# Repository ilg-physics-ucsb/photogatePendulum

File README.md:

# Photogate Pendulum

This repository should hold everything related to the photgates made by the ILG for recording more precise data on a pendulum setup. These photogates were made using off the shelf components from adafruit and amazon and mcmaster using a 3D printed case and a CNC milled PCB. For information on components visit the documentation folder, for information on the case or the ciruit visit the hardware folder and for information on the code visit the code folder. 

## Assembly Instructions

**Materials required** 

* **Integrated Circuits**
* 1x [Adafruit ItsyBitsy M0](https://www.digikey.com/en/products/detail/adafruit-industries-llc/3727/8346575?s=N4IgTCBcDaIIYBM4DMBOBXAlgFwAQ4GcBPXAI0JIFkAGEAXQF8g)
* 1x [LM358 Op Amp DIP-8](https://www.digikey.com/en/products/detail/texas-instruments/LM358P/277042)
* **Transistors**
* 6x [2N3904 NPN BJT](https://www.digikey.com/en/products/detail/diotec-semiconductor/2N3904/13164701)
* 1x [Phototransistor 3mm](https://www.digikey.com/en/products/detail/vishay-semiconductor-opto-division/BPW85A/4071264?s=N4IgTCBcDaIEIAUDqAOArAQRAXQL5A)
* **Diodes**
* 1x [IR LED 5mm](https://www.digikey.com/en/products/detail/vishay-semiconductor-opto-division/TSHF6210/4073549)
* 1x [Blue LED 5mm](https://www.digikey.com/en/products/detail/w%C3%BCrth-elektronik/151051BS04000/4490009)
* 1x [1N4148 Diode](https://www.digikey.com/en/products/detail/onsemi/1N4148/458603)
* **Capacitors**
* 5x [1nF](https://www.digikey.com/en/products/detail/kemet/R82EC1100SH50J/5141859)
* 1x [10nF](https://www.digikey.com/en/products/detail/kemet/R82EC2100AA50J/2571307)
* **Resistors**
* 3x [220Ω](https://www.digikey.com/en/products/detail/stackpole-electronics-inc/CF14JT220R/1741346) 
* 1x [1kΩ](https://www.digikey.com/en/products/detail/stackpole-electronics-inc/CF14JT1K00/1741314) 
* 2x [2.2kΩ](https://www.digikey.com/en/products/detail/stackpole-electronics-inc/CF14JT2K20/1741321)
* 9x [10kΩ](https://www.digikey.com/en/products/detail/stackpole-electronics-inc/CF14JT10K0/1741265)
* 2x [22kΩ](https://www.digikey.com/en/products/detail/stackpole-electronics-inc/CF14JT22K0/1741350)
* 3x [100kΩ](https://www.digikey.com/en/products/detail/stackpole-electronics-inc/CF14JT100K/1741263)
* 1x [220kΩ](https://www.digikey.com/en/products/detail/stackpole-electronics-inc/CF14JT220K/1741348)
* 2x [1MΩ](https://www.digikey.com/en/products/detail/stackpole-electronics-inc/CF14JT1M00/1741316) 
* **Tactile**
* 1x [Slide Switch SPDT H6mm](https://www.digikey.com/en/products/detail/same-sky-formerly-cui-devices/SLW-1298856-5A-RA-N-D/24399327)
* **Hardware**
* 1x [FR-1 single sided PCB blank](https://bantamtools.com/products/pcb?variant=32765656432719)
* 1x [1/32th in flat end mill](https://www.mcmaster.com/3066A49)
* 1x [USB-micro to USB-C cable](https://www.amazon.com/Type-C-Fasgear-Braided-Transfer-Compatible/dp/B07CHBR14C/ref=sr_1_3?crid=1D21SSNDEUH8P&dib=eyJ2IjoiMSJ9.PivcPrZAZSg21jQOPEd6xAvt9kDpQqMLWFVfht9Tn8mLNAZzDId2p5OxZ8LkejXtDpPKmn59rHOGYos2S7EBA3ajZcxPJMOG67W7Wv4sRvbQBcF_X5TXTdpQVGO5XpFmnKDs2Iv7MCWgjqrwcuj7gqHg7mUmrMKmFe2VphnZKjZm8xPE3bq8Ao8euvjV_39qhe8JMYmQLRm3Y08NwUTHYXBqhev11vDWwkCIPJ3RTQo.36eqddbM27o5PswbGuCB13i89pmYUmYZE5EW3kyz0KY&dib_tag=se&keywords=usb%2Bc%2Bto%2Busb%2Bmicro%2Bfasgear&qid=1762294692&sprefix=usb%2Bc%2Bto%2Busb%2Bmicro%2Bfasgear%2Caps%2C154&sr=8-3&th=1)
* 5x [M3x10mm screws](https://www.mcmaster.com/91290A115/)
* 5x [M3x6mm threaded inserts](https://www.mcmaster.com/94459A140/)
* 1x [1/4-20x0.226in threaded inserts](https://www.mcmaster.com/94459A736/)
* 1x [6in 1/4-20 mounting rod](https://www.mcmaster.com/97042A268/)

**Creating the PCB**

The heart of the photogate is its PCB housing all of the internal circuitry, all of which is housed on a PCB made to fit the case. All of the schematic and PCB design files can be found in a KiCAD oproject found [here](/Hardware/Circuit/photogatePendulumKiCAD/20AL_Pendulum_Photogate.kicad_pro). You can export the PCB design to a gerber file from here and send to a PCB manufacturer, or the baord has been designed to be able to be milled on a single sided PCB blank. To mill out the PCB you will need to export the edge cuts and bottom layer gerber files and the drill excellon file and then convert these to g-code. There is already a compiled g-code version of the scematic found [here](). This gcode was designed for use on our Bantam desktop milling machine, with a 1/32th in. flat end mill as the cutting tool. In formation on how to use this machine can be found [here](https://gaugeboson.physics.ucsb.edu/wiki/equipment/makerspace/cnc-machine/). Using this machine you can then cut out the PCB from the single sided PCB blank. The following is an image of the final PCB. The PCB May have some rough edges, leftover dust, or the copper may not have come off cleanly so there could be some post processing needed before soldering. You should use scotch brite to rub the surface and sides to get any excess dust and copper bits off. If the edges look rough you may also want to use a de-burring tool on them. 

**Soldering the Circuit**

The components are laid very densly in the PCB and in non standard orientations so here are some directions for how to best get this board together. Before you start soldering also make sure the surface has not tarnished from sitting for too long. If it is tarnished the solder wont stick well, so you will need to buff out the tarnish with some scotch brite before you begin. 

* You should first start [soldering all the components that lay flat](/Documentation/Instructions/SolderFlatComponents.jpg) on the board. These include the 0 ohm resistors (wires) and the horizontally laid resistors. Also make sure to clip the excess leads off of all the components between each step as these will not fit in the case. 

* Next you should put on the [IR LED](/Documentation/Instructions/SolderIRLED.jpg) and [phototransistor](/Documentation/Instructions/SolderPhototransistor.jpg). These sit at a right angle anf flush with the board so you will have to bend them into shape first before soldering. It is very important to get the wires off the back as [flush with the PCB](/Documentation/Instructions/SolderRightAngleParts.jpg) as possible.

* Next the [capacitors should be soldered](/Documentation//Instructions/SolderCapacitors.jpg) in. 

* The switch and the diode should be soldering in next. 

* The [transistors should be soldered in next](/Documentation//Instructions/SolderTransistors.jpg), being careful of which ones are NPN vs PNP as well as which direction they face. 

* Next you should [solder in the last of the reistors](/Documentation//Instructions/SolderUprightResistor.jpg). The transistors already in should make it easier to do this. Parts of the PCB are very desne though so you may still have to clip the leads partway through just to access the rest of the leads you need to solder in. 

* The [8 pin DIP socket comes next](/Documentation//Instructions/SolderIC.jpg), you may need tape to hold it in place though. Make sure that pin 1 is facing the correct direct when installing the socket. 

* Next up is [the Itsy Bitsy](/Documentation//Instructions/SolderItsyBitsy.jpg). The holes for the headers are a bit tight so you should solder the headers onto the itsy bitsy while they are already in the holes on the PCB. 

* Lastly is [the Blue LED](/Documentation//Instructions/SolderBlueLED.jpg). This must be set up above the PCB slightly so that it is flush with the top of the case. 

After you are finished soldering you should plug it in to make sure the photogate works correctly before flashing the code. The Blue LED should light up when the path between the IR LED and phototransistor is obstructed even when there is no code on the teensy. I often forget to install the LM358 into the IC socket so if it is not working first check that. If it is not working and that is not the problem then you should check your solder joints to make sure there isnt any bridging, or for any stray strands of copper leftover from milling. 

**Assembling the Case**

You will also need to 3D print the files for the case, the lid can be found [here](/Hardware//CAD/photogatePendulumLid.stl) and the base [here](/Hardware/CAD/photogatePendulumBase.stl). If you need to edit the case for any reason the raw fusion 360 file can be found [here](/Hardware/CAD/photogatePendulumFusion360.f3z). The file will need supports to print, and we used a 0.1mm layer height and 15% infill with black PLA on a powder coated bed for best results. After the print finishes you will need to remove the supports using pliers from both the bottom and side of the base, and depending on the print quality you may need to clean the print of ant [stringing or stray filament threads](/Documentation/Instructions/FinishedPrint.jpg). 

Now that the print is clean you need to insert all of the interior threaded inserts, these are the M3x6mm inerts. Place them as [shown](/Documentation/Instructions/ThreadedInserts.jpg), and then use a soldering iron to[ heat and push them into place](/Documentation/Instructions/SoldeingThreadedInserts.jpg). As you insert them be careful that they are placed centered on their holes, that they are inserted straight, and that you dont leave any plastic up above the plane they should be flush with. When finished it should look like [this](/Documentation/Instructions/FinalThreadedInserts.jpg). Once the interior threadedinserts are finished you can attached the USB-C to micro-USB cable to the finsished PCB and [place it inside the case](/Documentation/Instructions/ClosingCase.jpg) and screw it together with the M3x10mm screws. 

The last step in assembly is to insert the [1/4-20 threaded insert](/Documentation/Instructions/Quarter20Insert.jpg) for the mounting rod. Since this insert is so large and shallow it is slightly precarious to heat it up with the soldering iron since you cant stick it down the center as you usually would, instaed you need to lay it across the insert and push it down sideways as seen [here](/Documentation/Instructions/SolderingQuarter20.jpg). This process can take some time as the heat transfer is not great, you just should be careful to melt the exterior of the box as little as possible outside the are needed. Once the inser is in s far as it can reasonably go you should [thread in the mounting rod while it is still warm](/Documentation/Instructions/ThreadingMountingRod.jpg) and the plastic is malleable so that the interior plastic forms around the tip giving it a snug fit. 

**Flashing the Code**

The code for this system was made in Arduino IDE and requires the built in libraries to fuction properly, so to flash the code you must use this IDE. The raw .ino file can be found [here](/Code/photogatePendulum/photogatePendulum.ino). To properly compile the code you will also need to install the core for the ItsyBitsy through Arduino IDE, to do this you will need to follow the steps in the ItsyBitsy datasheet. The code also requires a few libraries to work, you can find all of these [here](/Code/Libraries). You will need copy these over into the libraries sub-folder of wherever the Aduino IDE stores its files, often in "~/documents/Arduino/". From here you should be able to compile and upload the code to the ItsyBitsy when it is plugged into your computer.

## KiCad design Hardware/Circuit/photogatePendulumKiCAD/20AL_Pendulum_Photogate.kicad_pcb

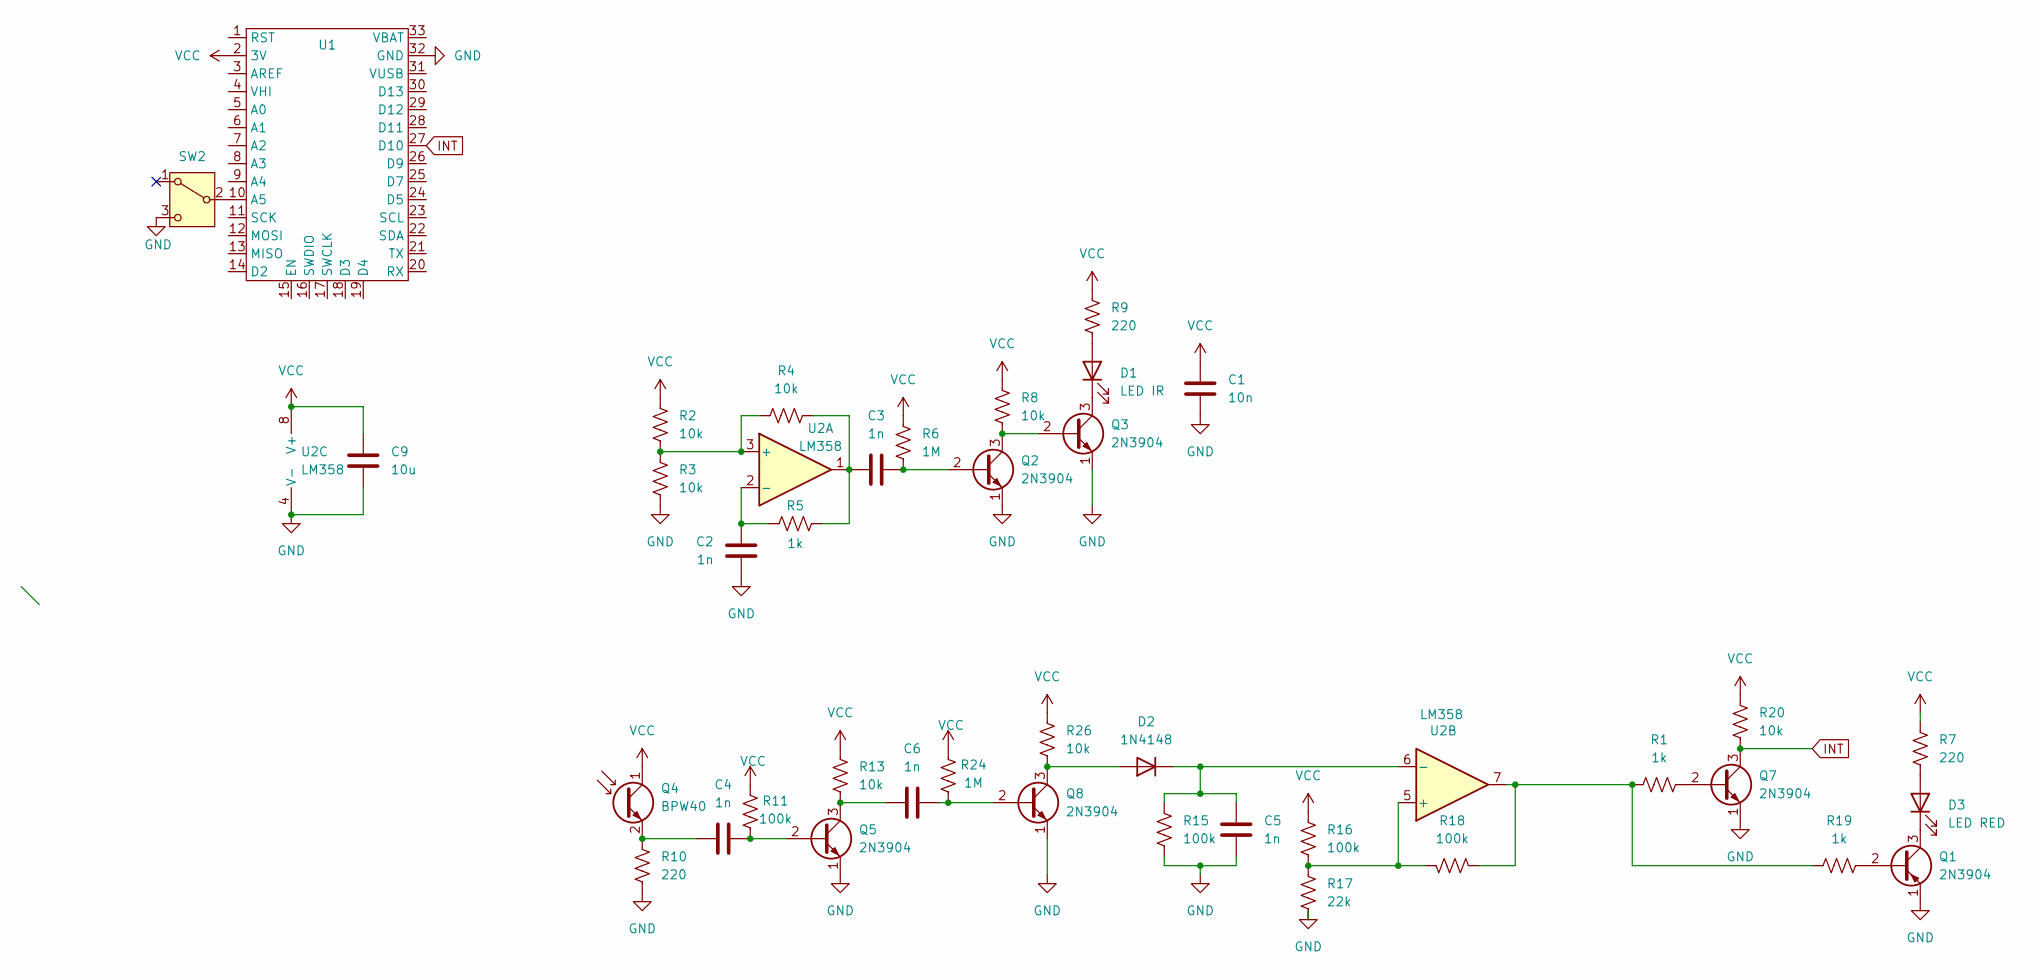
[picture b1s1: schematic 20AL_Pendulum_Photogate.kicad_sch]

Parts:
C1: 10n; C_Rect_L7.2mm_W2.5mm_P5.00mm_FKS2_FKP2_MKS2_MKP2
C2, C3, C4, C5, C6: 1n; C_Rect_L7.2mm_W2.5mm_P5.00mm_FKS2_FKP2_MKS2_MKP2
C9: 10u; C_Rect_L7.2mm_W2.5mm_P5.00mm_FKS2_FKP2_MKS2_MKP2
D1: LED IR; LED_D5.0mm_Horizontal_O3.81mm_Z3.0mm
D2: 1N4148; D_DO-35_SOD27_P7.62mm_Horizontal
D3: LED RED; LED_D5.0mm_Clear
Q1, Q2, Q3, Q5, Q7, Q8: 2N3904; TO-92_Inline_Wide
Q4: BPW40; LED_D3.0mm_Horizontal_O3.81mm_Z2.0mm
R1, R5: 1k; R_Axial_DIN0207_L6.3mm_D2.5mm_P7.62mm_Horizontal
R2: 10k; R_Axial_DIN0207_L6.3mm_D2.5mm_P10.16mm_Horizontal
R3, R4, R8, R13, R26: 10k; R_Axial_DIN0207_L6.3mm_D2.5mm_P7.62mm_Horizontal
R6, R24: 1M; R_Axial_DIN0207_L6.3mm_D2.5mm_P7.62mm_Horizontal
R7, R9: 220; R_Axial_DIN0207_L6.3mm_D2.5mm_P10.16mm_Horizontal
R10: 220; R_Axial_DIN0207_L6.3mm_D2.5mm_P7.62mm_Horizontal
R11, R15, R16, R18: 100k; R_Axial_DIN0207_L6.3mm_D2.5mm_P7.62mm_Horizontal
R17: 22k; R_Axial_DIN0207_L6.3mm_D2.5mm_P7.62mm_Horizontal
R19: 1k; R_Axial_DIN0207_L6.3mm_D2.5mm_P10.16mm_Horizontal
R20: 10k; R_Axial_DIN0207_L6.3mm_D2.5mm_P15.24mm_Horizontal
SW2: SW_SPDT; SlideSwitch_SPDT
U1: AdafruitItsyBitsyM0
U2: LM358; DIP-8_W7.62mm_Socket_LongPads

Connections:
GND: C1.1, C2.2, C5.1, C9.2, Q1.1 (E), Q2.1 (E), Q3.1 (E), Q5.1 (E), Q7.1 (E), Q8.1 (E), R3.2, R10.2, R15.2, R17.2, SW2.3 (C), U1.32 (GND), U2.4 (V-)
INT: Q7.3 (C), R20.2, U1.27 (D10)
unnamed: C3.1, R4.2, R5.2, U2.1
unnamed: D1.2 (A), R9.2
unnamed: D1.1 (K), Q3.3 (C)
unnamed: D2.2 (A), Q8.3 (C), R26.2
unnamed: C5.2, D2.1 (K), R15.1, U2.6 (-)
unnamed: D3.2 (A), R7.1
unnamed: D3.1 (K), Q1.3 (C)
unnamed: Q1.2 (B), R19.2
unnamed: C3.2, Q2.2 (B), R6.2
unnamed: Q2.3 (C), Q3.2 (B), R8.2
unnamed: C4.1, Q4.2 (E), R10.1
unnamed: C4.2, Q5.2 (B), R11.2
unnamed: C6.1, Q5.3 (C), R13.2
unnamed: Q7.2 (B), R1.2
unnamed: C6.2, Q8.2 (B), R24.2
unnamed: R1.1, R18.2, R19.1, U2.7
unnamed: SW2.2 (B), U1.10 (A5)
unnamed: R2.2, R3.1, R4.1, U2.3 (+)
unnamed: C2.1, R5.1, U2.2 (-)
unnamed: R16.1, R17.1, R18.1, U2.5 (+)
VCC: C1.2, C9.1, Q4.1 (C), R2.1, R6.1, R7.2, R8.1, R9.1, R11.1, R13.1, R16.2, R20.1, R24.1, R26.1, U1.2 (3V), U2.8 (V+)

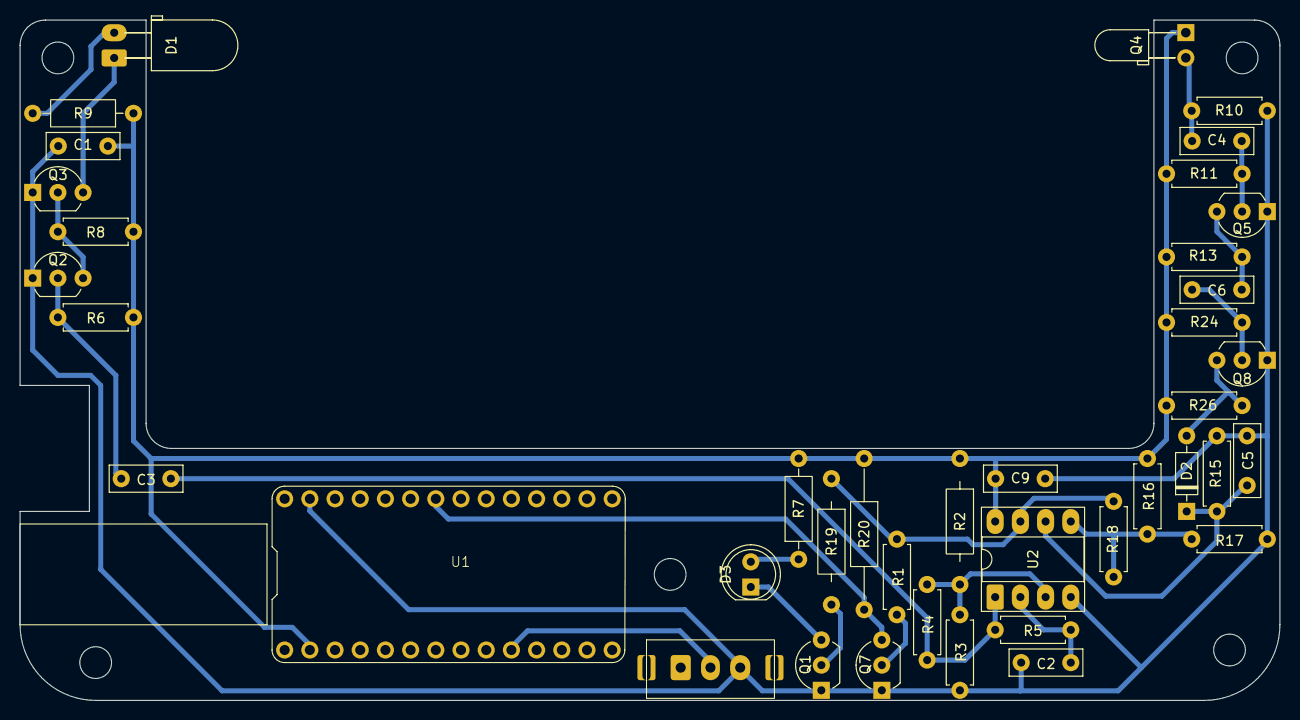
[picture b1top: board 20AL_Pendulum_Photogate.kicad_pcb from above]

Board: 2 copper layers, 127.0 x 68.6 mm, 40 parts (0 on the bottom side), 23 nets.

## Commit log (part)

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2025-11-04 Init the repo
2025-11-04 Start materials list
2025-11-07 start instructions
2025-11-20 Add soldering to readme
2025-12-01 Add instruction Pictures
2025-12-02 link to images in read me
2025-12-10 Finish the read me instructions
2026-06-10 Finalize design
